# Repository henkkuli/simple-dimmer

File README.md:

Simple dimmer
=============

This is a simple LED dimmer PCB based on the common 555 timer IC.

The motivation behind this project was to introduce my friend into the world of electronics. As we have a boat with way too bright LED strip, a dimmer would be both a simple first project and still very useful. My friend designed the schematic based on the [555 datasheet](https://www.ti.com/lit/ds/symlink/lm555.pdf) and [a tutorial on PWM dimmers](https://www.electronicshub.org/pwm-led-dimmer-using-ne555/). Our next step is to manufacture the PCB at our university's electronics lab. This is also going to be an experiment for me to see how good are the facilities, and what does the end result look like. The final step is to let my friend solder all components on the PCB.

Pictures
--------

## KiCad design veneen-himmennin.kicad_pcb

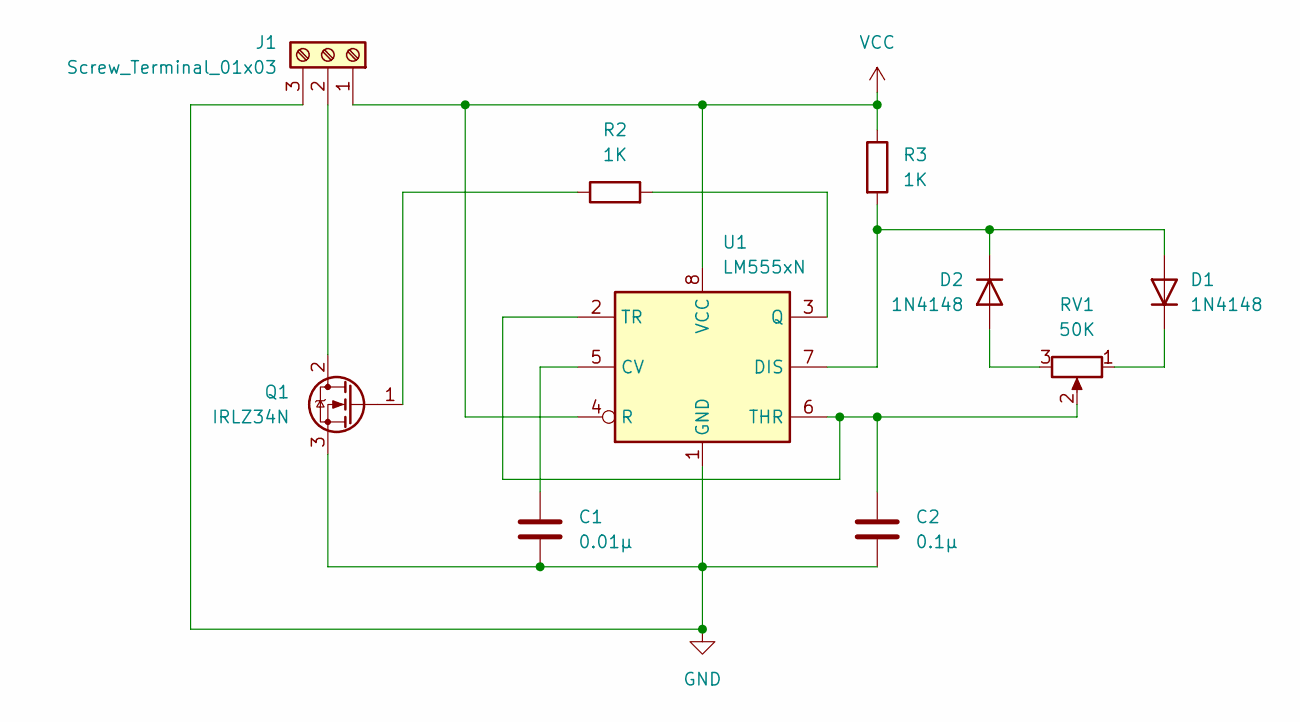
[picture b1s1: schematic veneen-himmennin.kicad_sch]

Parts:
C1: 0.01µ; C_Disc_D5.0mm_W2.5mm_P5.00mm
C2: 0.1µ; C_Disc_D5.0mm_W2.5mm_P2.50mm
D1, D2: 1N4148; D_DO-35_SOD27_P7.62mm_Horizontal
J1: Screw_Terminal_01x03; TerminalBlock_Phoenix_MKDS-1,5-3-5.08_1x03_P5.08mm_Horizont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
Q1: IRLZ34N; TO-220-3_Vertical
R2, R3: 1K; R_Axial_DIN0207_L6.3mm_D2.5mm_P7.62mm_Horizontal
RV1: 50K; Potentiometer_Omeg_PC16BU_Vertical
U1: LM555xN; DIP-8_W7.62mm

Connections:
GND: C1.2, C2.2, J1.3, Q1.3 (S), U1.1 (GND)
unnamed: D1.2 (A), D2.1 (K), R3.2, U1.7 (DIS)
unnamed: D1.1 (K), RV1.1
unnamed: D2.2 (A), RV1.3
unnamed: J1.2, Q1.2 (D)
unnamed: Q1.1 (G), R2.1
unnamed: C1.1, U1.5 (CV)
unnamed: R2.2, U1.3 (Q)
unnamed: C2.1, RV1.2, U1.2 (TR), U1.6 (THR)
VCC: J1.1, R3.1, U1.4 (R), U1.8 (VCC)

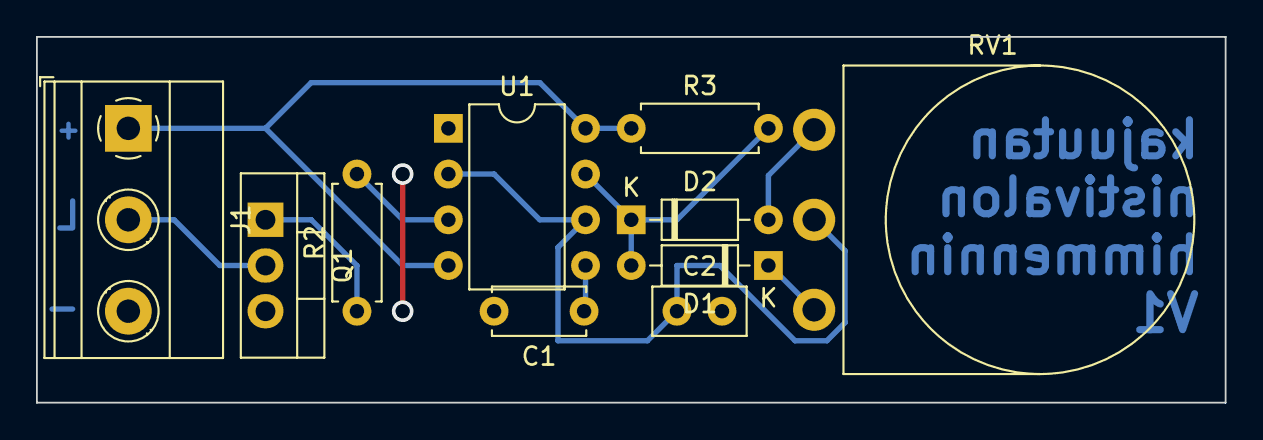
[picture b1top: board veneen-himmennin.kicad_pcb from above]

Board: 2 copper layers, 66.0 x 20.3 mm, 10 parts (0 on the bottom side), 10 nets.

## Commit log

2023-05-22 Add README
